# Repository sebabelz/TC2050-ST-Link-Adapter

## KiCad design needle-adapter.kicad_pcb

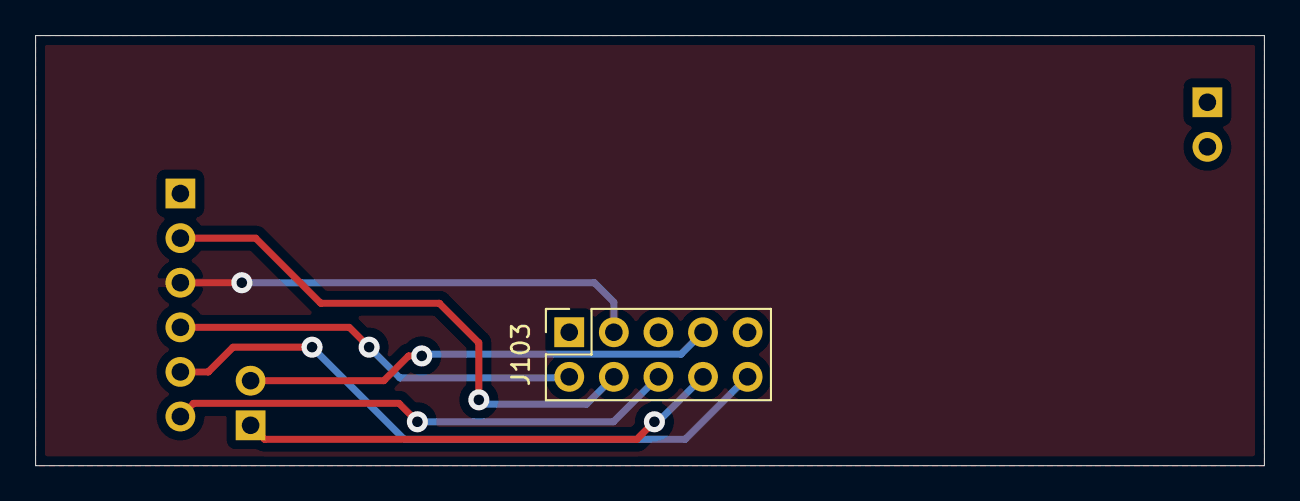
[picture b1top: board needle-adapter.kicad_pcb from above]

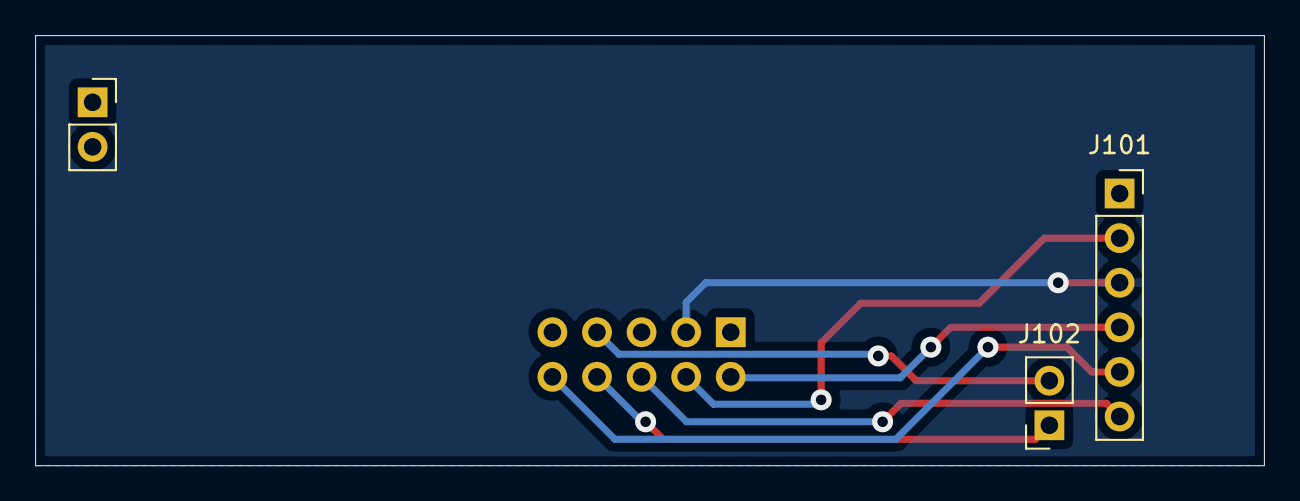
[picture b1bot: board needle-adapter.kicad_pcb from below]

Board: 2 copper layers, 70.0 x 24.5 mm, 4 parts (3 on the bottom side), 7 nets.

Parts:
J101: Conn_01x06; PinSocket_1x06_P2.54mm_Vertical
J102, J104: Conn_01x02; PinSocket_1x02_P2.54mm_Vertical
J103: Conn_02x05_Top_Bottom; PinSocket_2x05_P2.54mm_Vertical

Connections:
/GND: J101.3, J103.3
/RX: J102.1, J103.8
/SWDCLK: J101.2, J103.4
/SWDIO: J101.4, J103.2
/SWO: J101.6, J103.6
/TX: J102.2, J103.7
/~RESET~: J101.5, J103.10

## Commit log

2021-08-16 added gitignore and finished pcb
